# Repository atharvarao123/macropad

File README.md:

# Macropad
Custom 2x2 Macropad designed in KiCad.

## Hardware
 
- ESP32 DevKitC
- 2x2 (originally planned 3x3) mechanical switch matrix
- 1N4148 diodes, one per switch, for anti-ghosting

## Firmware (ESP-IDF)
 
Scans the matrix continuously, debounces with a combined state-check + time-window approach (needed since the scan loop runs way faster than a human can press a key), and logs `row col` over serial on every clean press.

## PC-side listener (Python)
 
Reads the serial output, parses out the row/col pair, and dispatches to whatever action is mapped for that key . Is in `communication/`.

## Images
 
**PCB**

**Assembled Macropad**

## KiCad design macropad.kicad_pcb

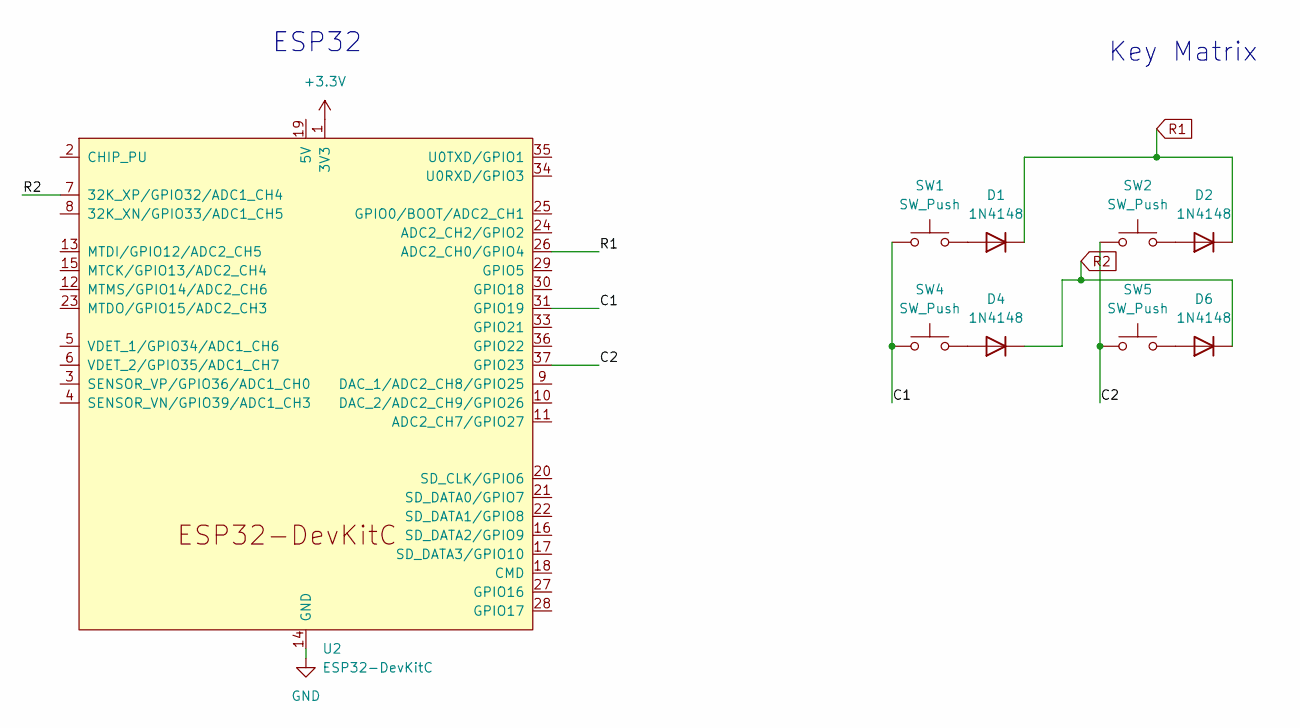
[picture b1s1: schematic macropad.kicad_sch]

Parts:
D1, D2, D4, D6: 1N4148; D_DO-35_SOD27_P7.62mm_Horizontal
SW1, SW2, SW4, SW5: SW_Push; SW_MX
U2: ESP32-DevKitC

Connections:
+3.3V: U2.1 (3V3)
/C1: SW1.1, SW4.1, U2.31 (GPIO19)
/C2: SW2.1, SW5.1, U2.37 (GPIO23)
GND: U2.14 (GND), U2.32 (GND), U2.38 (GND)
unnamed: D1.2 (A), SW1.2
unnamed: D2.2 (A), SW2.2
unnamed: D4.2 (A), SW4.2
unnamed: D6.2 (A), SW5.2
R1: D1.1 (K), D2.1 (K), U2.26 (ADC2_CH0/GPIO4)
R2: D4.1 (K), D6.1 (K), U2.7 (32K_XP/GPIO32/ADC1_CH4)

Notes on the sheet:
Key Matrix
ESP32

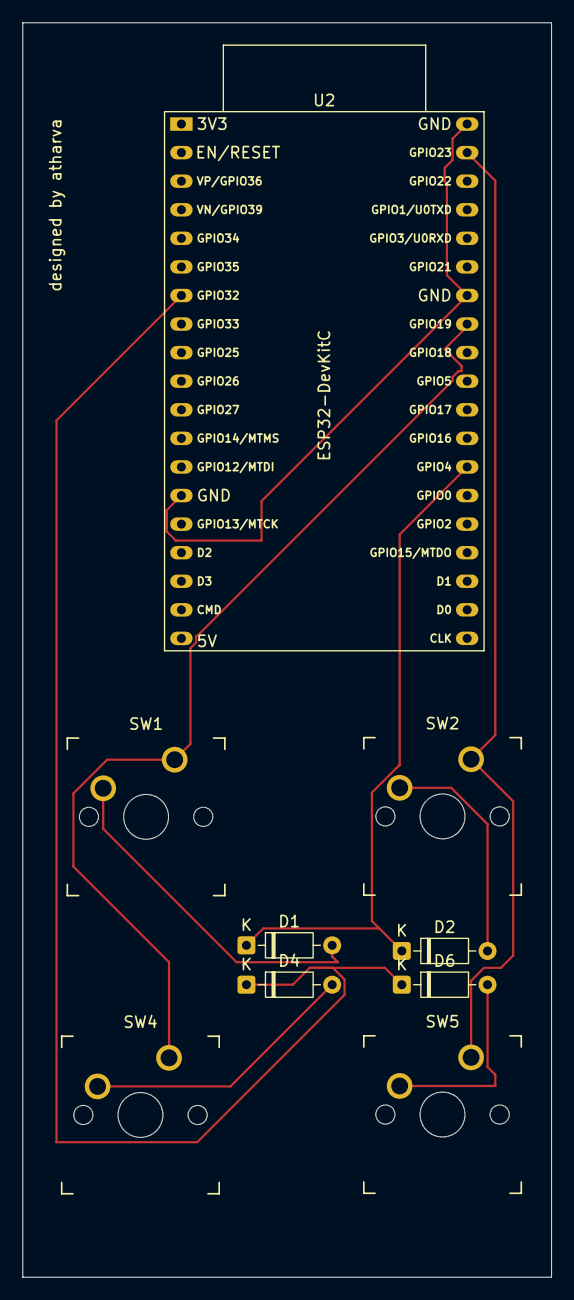
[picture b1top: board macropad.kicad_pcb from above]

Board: 2 copper layers, 47.0 x 111.5 mm, 9 parts (0 on the bottom side), 9 nets.
